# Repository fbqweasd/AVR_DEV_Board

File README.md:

# AVR 개발 보드 설계

회로 설계와 artwork를 공부하기 위해서 학교에서 사용하는 LK임베디드의 AVR보드를 본따서 AVR개발 보드를 설계하였습니다. 

## 회로도

 이번에 회로도를 그릴때는 보기 좋게 모듈화를 하여서 그렸습니다. 아직 kicad의 사용법이 익숙하지 않아서 회로가 제대로 그려지지 않은 부분이 있을 수 있습니다.

저번 보다는 훨신 보기 좋고 멋있게 설계를 하였는데 핀 구성, 커넥터 구성은 LK임베디드의 회로를 참고하여 사용을 하였습니다.

## ArtWork

상용화를 하는 회로도에서 많이 참고하여 설계를 하여서 ArtWork를 할때 보다 더 복잡하지 않고 효율적이게 그릴 수 있었습니다.

# 후기 
이번 설계를 하면서 만일 다른 회로도를 참고 하지 않고 만들면 어떻게 되었을까? 라는 생각을 하였습니다. 만일 그랬다면 저번에 만든 회로 보다 훨신 복잡하고 더럽게 만들어져서 보여주기 부끄러울 정도의 회로가 나왔을 거라고 생각합니다. 

회로 설계를 다 하고 느낀것이 설계를 하기전에 미리 큰 그림을 보면서 설계를 해야 예쁜회로가 나온다고 느겼습니다. 그래서 다음번 엔 설계를 하기전에 미리 종이에 구상도를 그려보고 datasheet를 참고하면서 부품의 위치를 정해가면서 설계를 해야 되겠다고 생각ㅇ르 하였습니다.

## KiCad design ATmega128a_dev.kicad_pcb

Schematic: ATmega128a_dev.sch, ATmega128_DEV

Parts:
10k1: R; R_0603_1608Metric
16Hz1: Crystal; Crystal_DS26_D2.0mm_L6.0mm_Horizontal
C1, C2: 22pF; CP_Elec_4x3
C3, C4: 0.1uF; C_0603_1608Metric
D1: D; D_0603_1608Metric
D2: LED; LED_0805_2012Metric_Castellated
J1, J3: Conn_01x32_Male; PinSocket_1x32_P2.00mm_Vertical
J2: USART0; Hirose_DF13-06P-1.25DSA_1x06_P1.25mm_Vertical
J4: UART1; PinSocket_1x04_P1.00mm_Vertical
J5: Ateml AVRISP; PinHeader_2x05_P2.00mm_Vertical_SMD
J6: Barrel_Jack_Switch; BarrelJack_CUI_PJ-102AH_Horizontal
L1: L; L_Bourns_SRR1260
POWER_C1: 0.1uF; C_0603_1608Metric
POWER_CP1: 47uF/25V; CP_Elec_4x5.8
POWER_SW1: SW_DIP_x01; SW_DIP_x1_W7.62mm_Slide
R1: 330R; R_0603_1608Metric
RESET_SW1: SW_DIP_x01; SW_DIP_x1_W7.62mm_Slide
U1: L7805; TO-220-3_Vertical
U2: ATmega128-16AU; TQFP-64_14x14mm_P0.8mm

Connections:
+12V: D1.2, POWER_SW1.2
AVCC: C4.1, J3.32, L1.2, U2.64 (AVCC)
GND: C1.2, C2.2, C3.2, C4.2, D2.1, J1.11, J2.1, J3.21, J3.31, J4.3, J5.4, J5.6, J5.8, J5.10, J6.2, J6.3, POWER_C1.2, POWER_CP1.2, RESET_SW1.2, U1.2, U2.22 (GND), U2.53 (GND), U2.63 (GND)
MISO: J5.9
MOSI: J1.21, J5.1, U2.12 (PB2)
unnamed: 10k1.2, RESET_SW1.1
unnamed: D1.1, POWER_C1.1, POWER_CP1.1, U1.1
unnamed: D2.2, R1.2
unnamed: J6.1, POWER_SW1.1
PA0: J3.19, U2.51 (PA0)
PA1: J3.18, U2.50 (PA1)
PA2: J3.17, U2.49 (PA2)
PA3: J3.16, U2.48 (PA3)
PA4: J3.15, U2.47 (PA4)
PA5: J3.14, U2.46 (PA5)
PA6: J3.13, U2.45 (PA6)
PA7: J3.12, U2.44 (PA7)
PB0: J1.23, U2.10 (PB0)
PB1: J1.22, J2.3, J5.7, U2.11 (PB1)
PB3: J1.20, U2.13 (PB3)
PB4: J1.19, U2.14 (PB4)
PB5: J1.18, U2.15 (PB5)
PB6: J1.17, U2.16 (PB6)
PB7: J1.16, U2.17 (PB7)
PC0: J3.3, U2.35 (PC0)
PC1: J3.4, U2.36 (PC1)
PC2: J3.5, U2.37 (PC2)
PC3: J3.6, U2.38 (PC3)
PC4: J3.7, U2.39 (PC4)
PC5: J3.8, U2.40 (PC5)
PC6: J3.9, U2.41 (PC6)
PC7: J3.10, U2.42 (PC7)
PD0: J1.8, U2.25 (PD0)
PD1: J1.7, U2.26 (PD1)
PD2: J1.6, J4.2, U2.27 (PD2)
PD3: J1.5, J4.1, U2.28 (PD3)
PD4: J1.4, U2.29 (PD4)
PD5: J1.3, U2.30 (PD5)
PD6: J1.2, U2.31 (PD6)
PD7: J1.1, U2.32 (PD7)
PE0: J1.31, J2.5, U2.2 (PE0)
PE1: J1.30, J2.4, U2.3 (PE1)
PE2: J1.29, U2.4 (PE2)
PE3: J1.28, U2.5 (PE3)
PE4: J1.27, U2.6 (PE4)
PE5: J1.26, U2.7 (PE5)
PE6: J1.25, U2.8 (PE6)
PE7: J1.24, U2.9 (PE7)
PEN: J1.32, U2.1 (~PEN)
PF0: J3.29, U2.61 (PF0)
PF1: J3.28, U2.60 (PF1)
PF2: J3.27, U2.59 (PF2)
PF3: J3.26, U2.58 (PF3)
PF4: J3.25, U2.57 (PF4)
PF5: J3.24, U2.56 (PF5)
PF6: J3.23, U2.55 (PF6)
PF7: J3.22, U2.54 (PF7)
PG0: J3.1, U2.33 (PG0)
PG1: J3.2, U2.34 (PG1)
PG2: J3.11, U2.43 (PG2)
PG3: J1.15, U2.18 (PG3)
PG4: J1.14, U2.19 (PG4)
RESET: J1.13, J2.2, J5.5, U2.20 (~RESET)
XTAL1: 16Hz1.1, C1.1, J1.9, U2.24 (XTAL1)
XTAL2: 16Hz1.2, C2.1, J1.10, U2.23 (XTAL2)

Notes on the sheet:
ATmega128_Pin
Clock
POWER
RESET
USART0
AVRISP
UART1
POWER_LED
AVCC
CONN_PIN

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
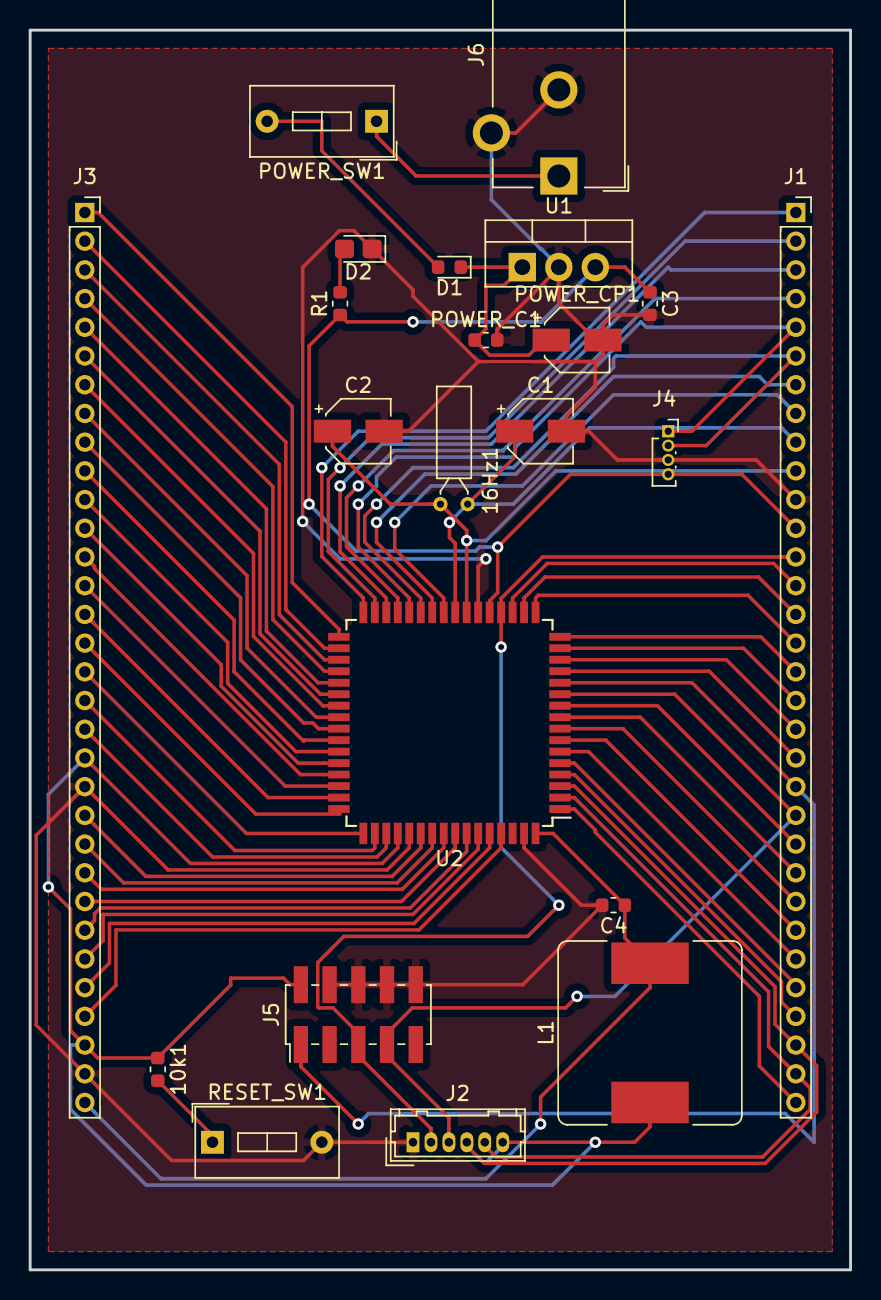
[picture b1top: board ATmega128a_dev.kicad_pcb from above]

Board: 2 copper layers, 57.1 x 86.4 mm, 22 parts (0 on the bottom side), 65 nets.

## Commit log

2018-11-19 fin_digin
2018-11-19 Readme update
